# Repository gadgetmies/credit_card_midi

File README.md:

# Credit Card MIDI Controllers

Arduino based, credit card sized, capacitive touch sensing MIDI controllers.

Very much a work in progress. Contributions welcomed 😊!

USB board connector design by @Pinuct: https://github.com/Pinuct/Eagle_PCB_USB_connectors

More info: https://hackaday.io/project/177099-credit-card-midi

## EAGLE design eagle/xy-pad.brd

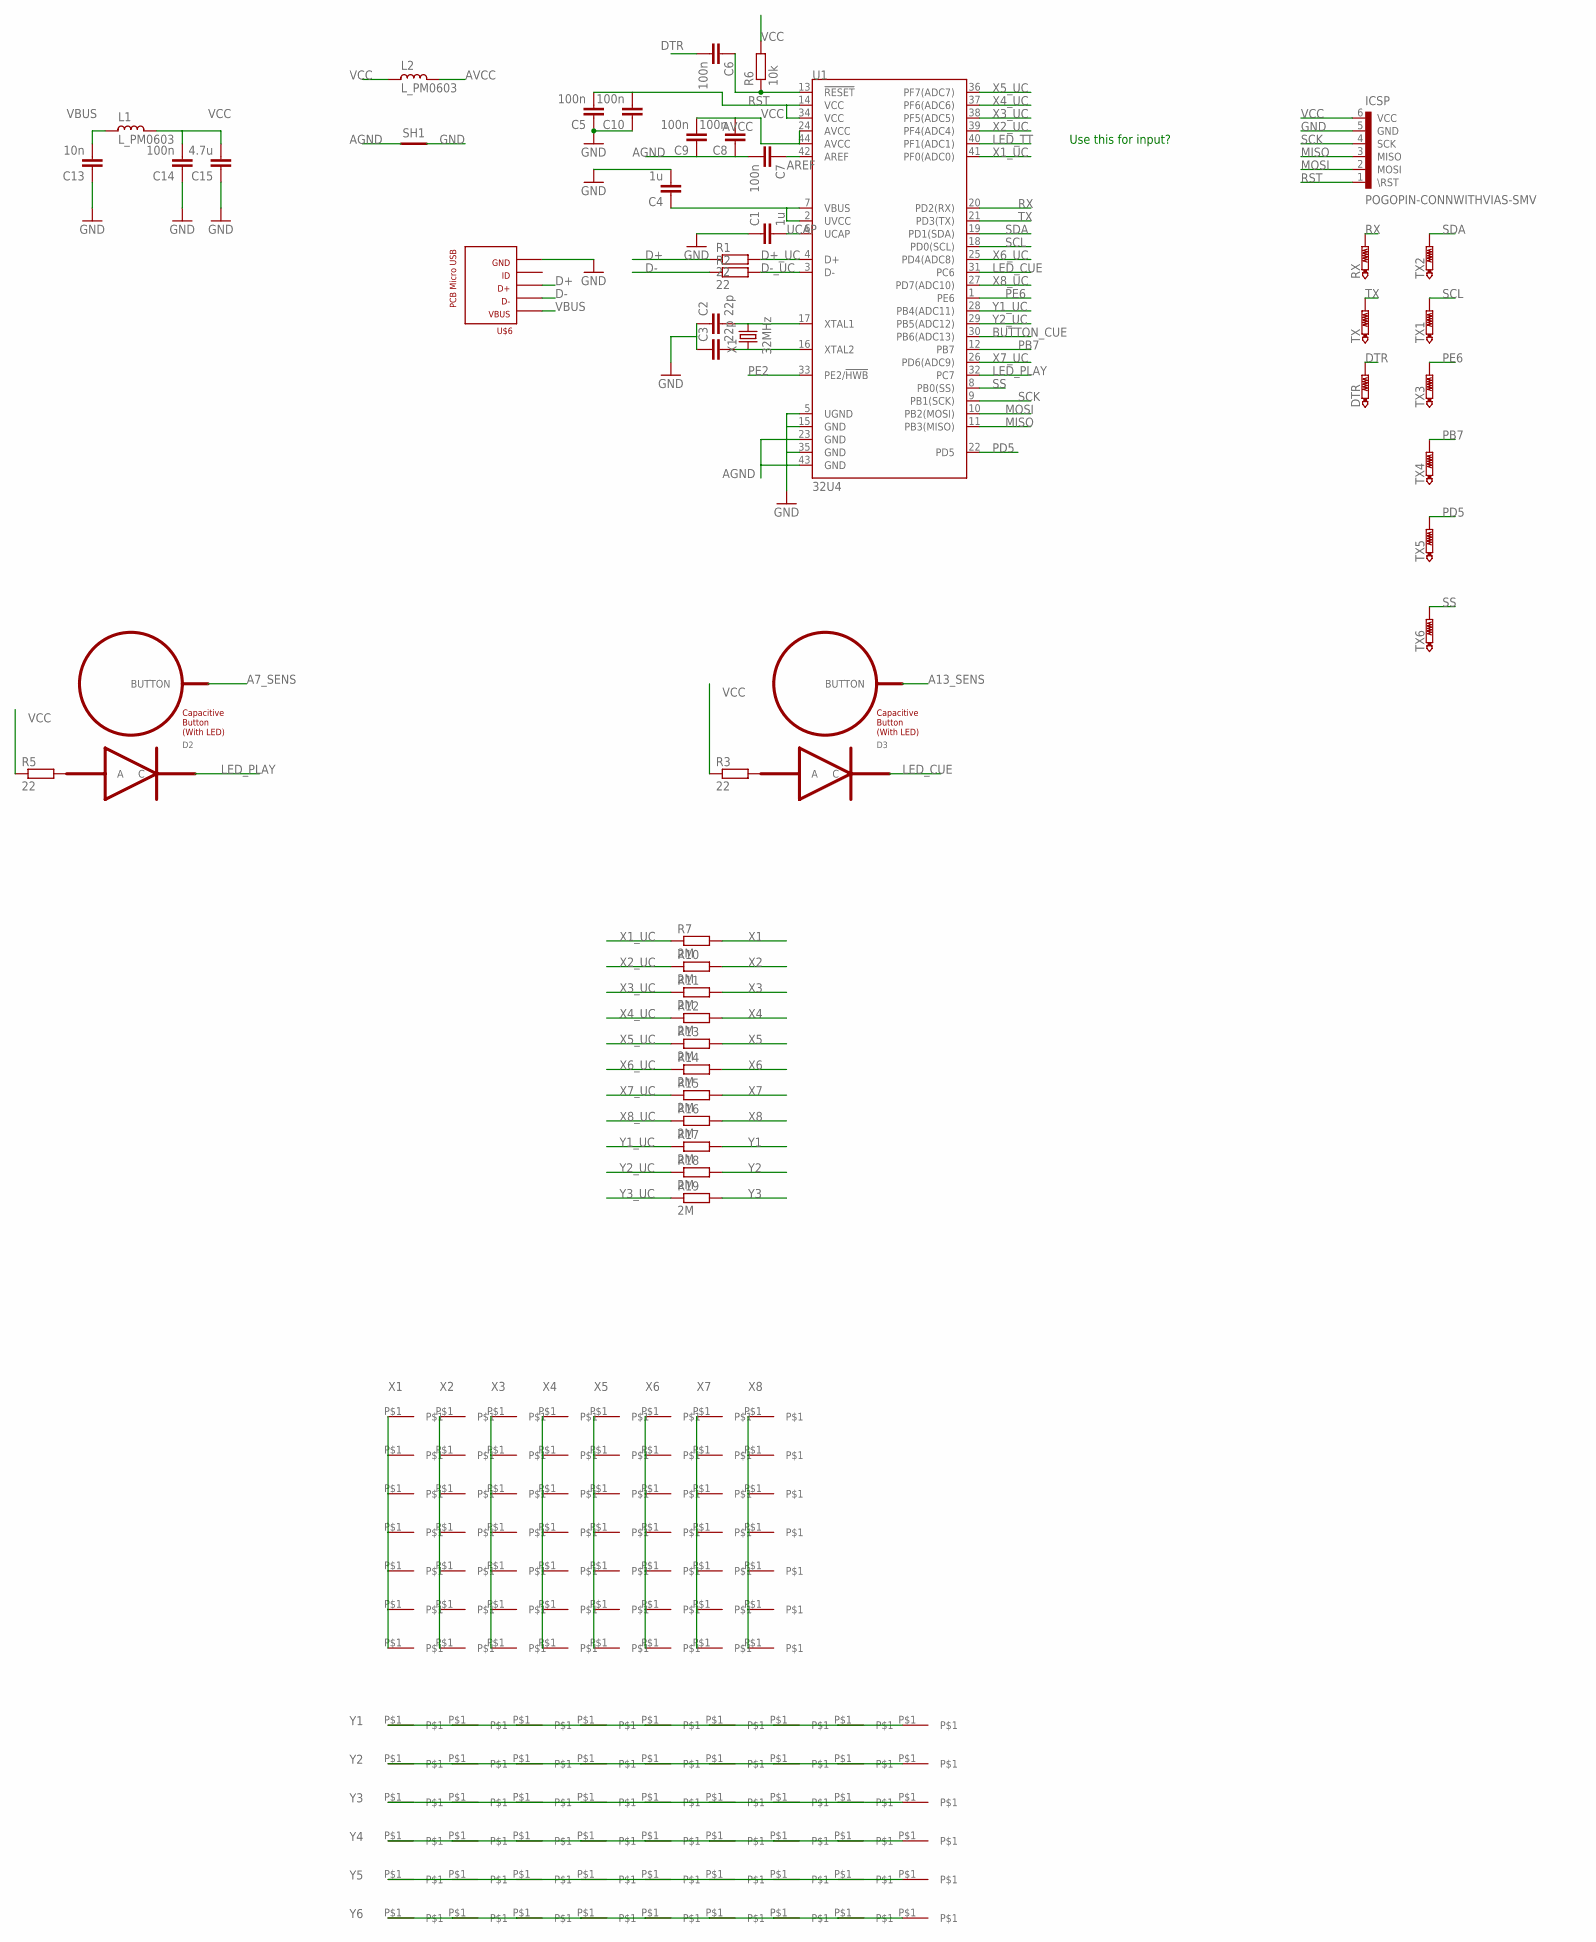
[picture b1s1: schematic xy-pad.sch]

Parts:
C1, C4: 1u; C0402
C2, C3: 22p; C0402
C5, C6, C7, C8, C9, C10, C14: 100n; C0402
C13: 10n; C0402
C15: 4.7u; C0402
D2, D3: LED_BUTTON
DTR: PTR1TP06R; TP06R
ICSP: POGOPIN-CONNWITHVIAS-SMV; POGOPROG-CONN-OH-SMALLERVIAS
L1, L2: L_PM0603; PM0603
R1, R2, R3, R5: 22; R0402
R6: 10k; R0402
R7, R10, R11, R12, R13, R14, R15, R16, R17, R18, R19: 2M; R0402
RX: PTR1TP06R; TP06R
SH1: SHORT; SHORT_TOP-6
TX, TX1, TX2, TX3, TX4, TX5, TX6: PTR1TP06R; TP06R
U1: 32U4; QFN-44
U$1, U$11, U$12, U$13, U$14, U$15, U$16, U$17, U$18, U$19, U$20, U$21, U$22, U$23, U$24, U$25, U$26, U$27, U$28, U$29, U$30, U$31, U$32, U$33, U$34, U$35, U$36, U$37, U$38, U$39, U$40, U$41, U$42, U$43, U$44, U$45, U$46, U$47, U$48, U$49, U$64, U$65, U$66, U$67, U$68, U$69, U$70, U$71, U$72, U$73, U$74, U$75, U$76, U$77, U$78, U$79, U$80, U$81, U$82, U$83, U$84, U$85, U$86, U$87, U$88, U$89, U$90, U$91, U$92, U$93, U$94, U$95, U$96, U$97, U$98, U$99, U$100, U$101, U$102, U$103, U$104, U$105: XY_PAD; DIAMOND_PAD
U$2, U$3, U$4, U$5, U$7, U$8, U$9, U$10, U$50, U$51, U$52, U$53, U$54, U$55, U$56, U$57, U$58, U$59, U$60, U$61, U$62, U$63, U$106, U$107, U$108, U$109, U$110, U$111: XY_PADTRIANGLE; TRIANGLE_PAD
U$6: PCB_MICRO_USB_BSS_2; USB_TYPE_B_SS_2
X1: 32MHz; CRYSTAL-SMD-2.0X1.6MM

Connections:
A7_SENS: D2.BUTTON
A13_SENS: D3.BUTTON
AGND: C7.2, C8.1, C9.1, SH1.1, U1.23 (GND), U1.43 (GND)
AREF: C7.1, U1.42 (AREF)
AVCC: C8.2, C9.2, L2.1, U1.24 (AVCC), U1.44 (AVCC)
BUTTON_CUE: U1.30 (PB6(ADC13))
D+: R1.1, U$6.3
D+_UC: R1.2, U1.4 (D+)
D-: R2.1, U$6.2
D-_UC: R2.2, U1.3 (D-)
DTR: C6.2, DTR.TP
GND: C1.1, C2.1, C3.1, C4.2, C5.1, C10.1, C13.1, C14.1, C15.1, ICSP.5 (GND), SH1.2, U1.5 (UGND), U1.15 (GND), U1.35 (GND), U$6.5
LED_CUE: D3.C, U1.31 (PC6)
LED_PLAY: D2.C, U1.32 (PC7)
LED_TT: U1.40 (PF1(ADC1))
MISO: ICSP.3 (MISO), U1.11 (PB3(MISO))
MOSI: ICSP.2 (MOSI), U1.10 (PB2(MOSI))
unnamed: D3.A, R3.2
unnamed: C2.2, U1.17 (XTAL1), X1.3 (2)
unnamed: C3.2, U1.16 (XTAL2), X1.1
unnamed: D2.A, R5.2
PB7: TX4.TP, U1.12 (PB7)
PD5: TX5.TP, U1.22 (PD5)
PE2: U1.33 (PE2/!HWB)
PE6: TX3.TP, U1.1 (PE6)
RST: C6.1, ICSP.1 (\RST), R6.1, U1.13 (!RESET)
RX: RX.TP, U1.20 (PD2(RX))
SCK: ICSP.4 (SCK), U1.9 (PB1(SCK))
SCL: TX1.TP, U1.18 (PD0(SCL))
SDA: TX2.TP, U1.19 (PD1(SDA))
SS: TX6.TP, U1.8 (PB0(SS))
TX: TX.TP, U1.21 (PD3(TX))
UCAP: C1.2, U1.6 (UCAP)
VBUS: C13.2, L1.2, U$6.1
VCC: C4.1, C5.2, C10.2, C14.2, C15.2, ICSP.6 (VCC), L1.1, L2.2, R3.1, R5.1, R6.2, U1.2 (UVCC), U1.7 (VBUS), U1.14 (VCC), U1.34 (VCC)
X1: R7.2, U$1.P$1, U$2.P$1, U$18.P$1, U$26.P$1, U$34.P$1, U$42.P$1, U$50.P$1
X1_UC: R7.1, U1.41 (PF0(ADC0))
X2: R10.2, U$3.P$1, U$11.P$1, U$19.P$1, U$27.P$1, U$35.P$1, U$43.P$1, U$51.P$1
X2_UC: R10.1, U1.39 (PF4(ADC4))
X3: R11.2, U$4.P$1, U$12.P$1, U$20.P$1, U$28.P$1, U$36.P$1, U$44.P$1, U$52.P$1
X3_UC: R11.1, U1.38 (PF5(ADC5))
X4: R12.2, U$5.P$1, U$13.P$1, U$21.P$1, U$29.P$1, U$37.P$1, U$45.P$1, U$53.P$1
X4_UC: R12.1, U1.37 (PF6(ADC6))
X5: R13.2, U$7.P$1, U$14.P$1, U$22.P$1, U$30.P$1, U$38.P$1, U$46.P$1, U$54.P$1
X5_UC: R13.1, U1.36 (PF7(ADC7))
X6: R14.2, U$8.P$1, U$15.P$1, U$23.P$1, U$31.P$1, U$39.P$1, U$47.P$1, U$55.P$1
X6_UC: R14.1, U1.25 (PD4(ADC8))
X7: R15.2, U$9.P$1, U$16.P$1, U$24.P$1, U$32.P$1, U$40.P$1, U$48.P$1, U$56.P$1
X7_UC: R15.1, U1.26 (PD6(ADC9))
X8: R16.2, U$10.P$1, U$17.P$1, U$25.P$1, U$33.P$1, U$41.P$1, U$49.P$1, U$57.P$1
X8_UC: R16.1, U1.27 (PD7(ADC10))
Y1: R17.2, U$63.P$1, U$69.P$1, U$75.P$1, U$81.P$1, U$87.P$1, U$93.P$1, U$99.P$1, U$105.P$1, U$111.P$1
Y1_UC: R17.1, U1.28 (PB4(ADC11))
Y2: R18.2, U$62.P$1, U$68.P$1, U$74.P$1, U$80.P$1, U$86.P$1, U$92.P$1, U$98.P$1, U$104.P$1, U$110.P$1
Y2_UC: R18.1, U1.29 (PB5(ADC12))
Y3: R19.2, U$61.P$1, U$67.P$1, U$73.P$1, U$79.P$1, U$85.P$1, U$91.P$1, U$97.P$1, U$103.P$1, U$109.P$1
Y3_UC: R19.1
Y4: U$60.P$1, U$66.P$1, U$72.P$1, U$78.P$1, U$84.P$1, U$90.P$1, U$96.P$1, U$102.P$1, U$108.P$1
Y5: U$59.P$1, U$65.P$1, U$71.P$1, U$77.P$1, U$83.P$1, U$89.P$1, U$95.P$1, U$101.P$1, U$107.P$1
Y6: U$58.P$1, U$64.P$1, U$70.P$1, U$76.P$1, U$82.P$1, U$88.P$1, U$94.P$1, U$100.P$1, U$106.P$1

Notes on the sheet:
Use this for input?

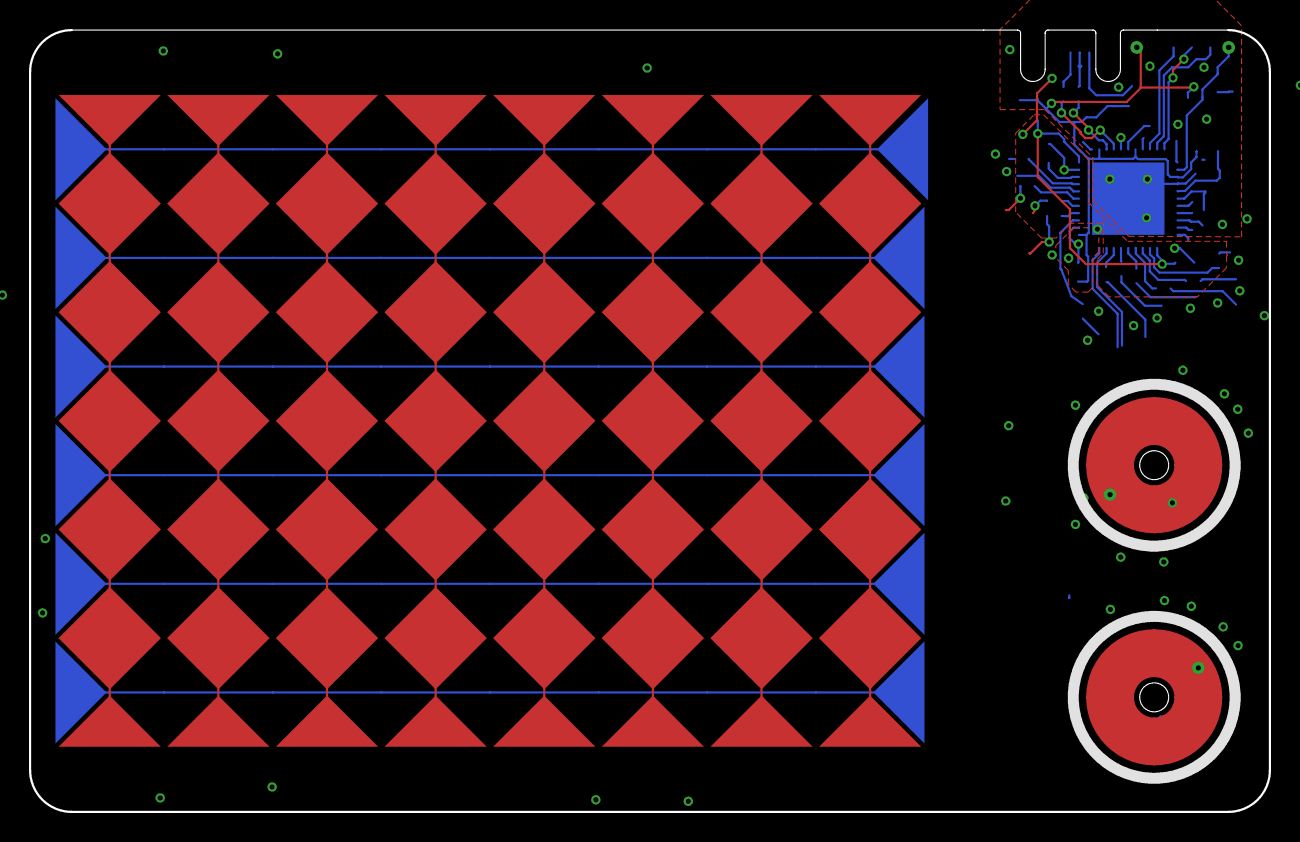
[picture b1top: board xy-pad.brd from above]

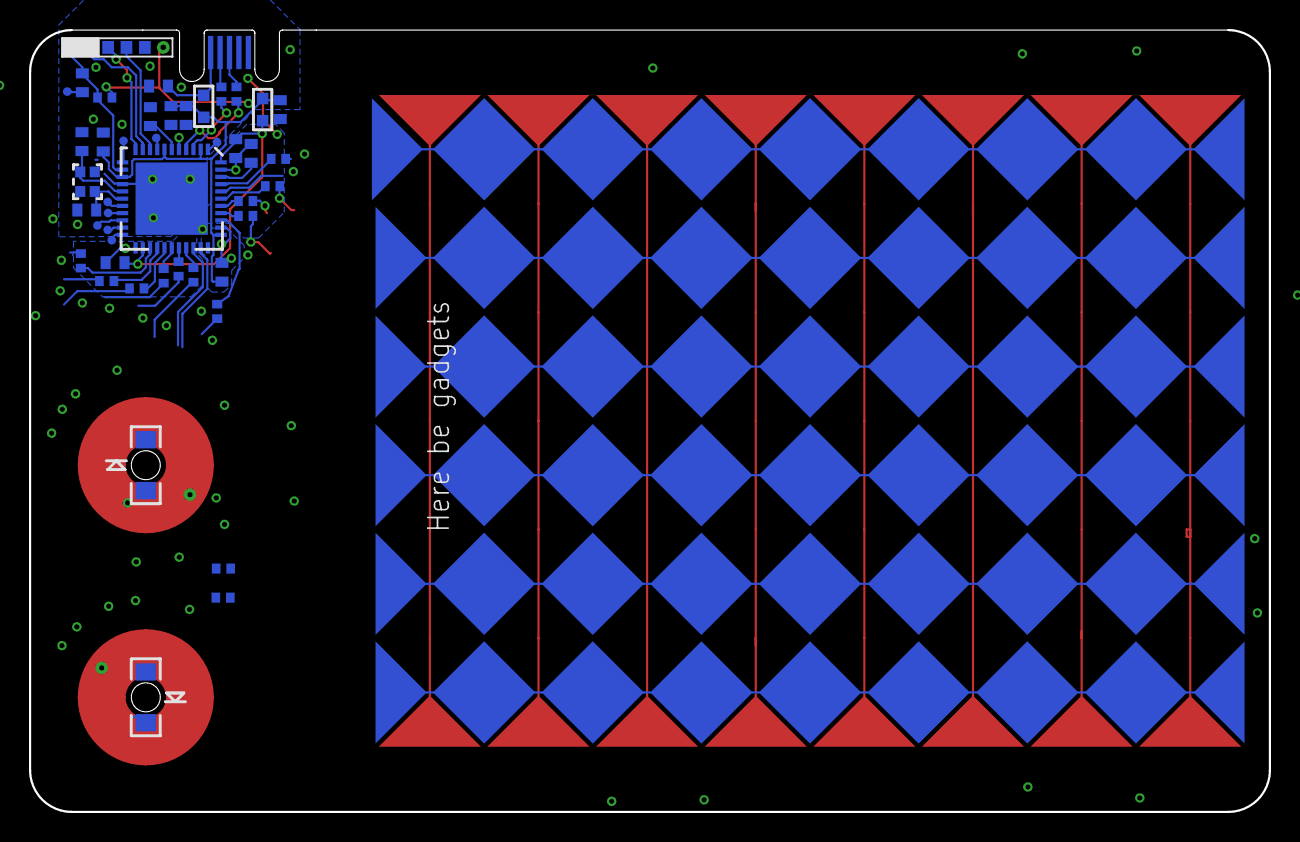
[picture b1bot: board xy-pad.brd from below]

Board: 2 copper layers, 85.6 x 54.0 mm, 157 parts (98 on the bottom side), 54 nets.

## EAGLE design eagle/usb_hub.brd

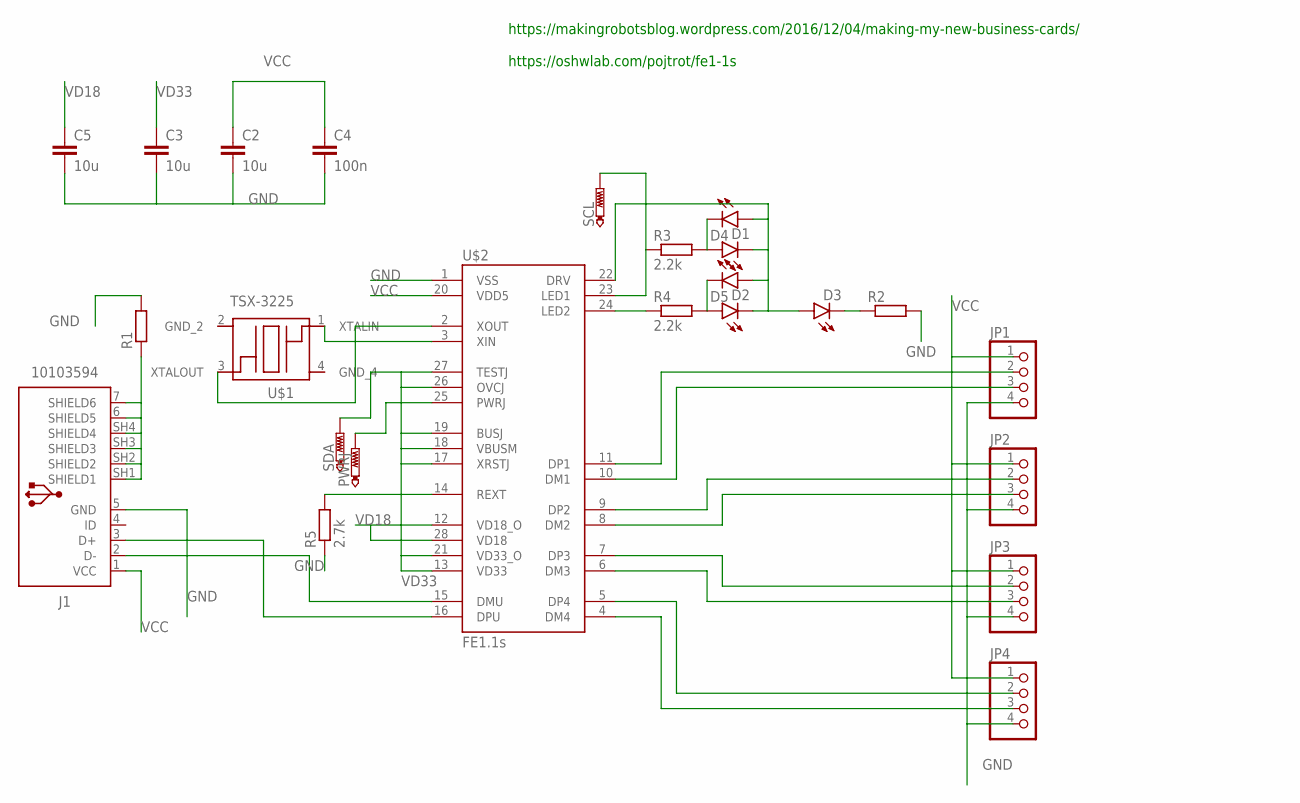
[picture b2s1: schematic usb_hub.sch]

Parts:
C2, C3, C5: 10u; C0805
C4: 100n; C0603
D1, D2, D3, D4, D5: LEDCHIP-LED0603; CHIP-LED0603
J1: 10103594
JP1, JP2, JP3, JP4: PINHD-1X4; 1X04
PWRJ: PTR1B1,27; B1,27
R1, R2: R-EU_R0603; R0603
R3, R4: 2.2k; R0603
R5: 2.7k; R0603
SCL: PTR1B1,27; B1,27
SDA: PTR1B1,27; B1,27
U$1: TSX-3225
U$2: FE1.1S; FE1.1S_SSOP-28

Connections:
GND: C2.2, C3.2, C4.2, C5.2, J1.5 (GND), JP1.4, JP2.4, JP3.4, JP4.4, R1.2, R2.2, R5.1, U$2.1 (VSS)
unnamed: J1.3 (D+), U$2.16 (DPU)
unnamed: J1.2 (D-), U$2.15 (DMU)
unnamed: U$1.1 (XTALIN), U$2.3 (XIN)
unnamed: U$1.3 (XTALOUT), U$2.2 (XOUT)
unnamed: D1.A, D4.C, R3.2
unnamed: D2.A, D5.C, R4.2
unnamed: JP4.3, U$2.4 (DM4)
unnamed: JP4.2, U$2.5 (DP4)
unnamed: JP3.3, U$2.6 (DM3)
unnamed: JP3.2, U$2.7 (DP3)
unnamed: JP2.3, U$2.8 (DM2)
unnamed: JP2.2, U$2.9 (DP2)
unnamed: JP1.3, U$2.10 (DM1)
unnamed: JP1.2, U$2.11 (DP1)
unnamed: R4.1, U$2.24 (LED2)
unnamed: D3.C, R2.1
unnamed: R3.1, SCL.TP, U$2.23 (LED1)
unnamed: D1.C, D2.C, D3.A, D4.A, D5.A, U$2.22 (DRV)
unnamed: PWRJ.TP, U$2.25 (PWRJ)
unnamed: R5.2, U$2.14 (REXT)
SHIELD2: J1.6 (SHIELD5), J1.7 (SHIELD6), J1.SH1 (SHIELD1), J1.SH2 (SHIELD2), J1.SH3 (SHIELD3), J1.SH4 (SHIELD4), R1.1
VCC: C2.1, C4.1, J1.1 (VCC), JP1.1, JP2.1, JP3.1, JP4.1, U$2.20 (VDD5)
VD18: C5.1, U$2.12 (VD18_O), U$2.28 (VD18)
VD33: C3.1, SDA.TP, U$2.13 (VD33), U$2.17 (XRSTJ), U$2.18 (VBUSM), U$2.19 (BUSJ), U$2.21 (VD33_O), U$2.26 (OVCJ), U$2.27 (TESTJ)

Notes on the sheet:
https://makingrobotsblog.wordpress.com/2016/12/04/making-my-new-business-cards/ https://oshwlab.com/pojtrot/fe1-1s

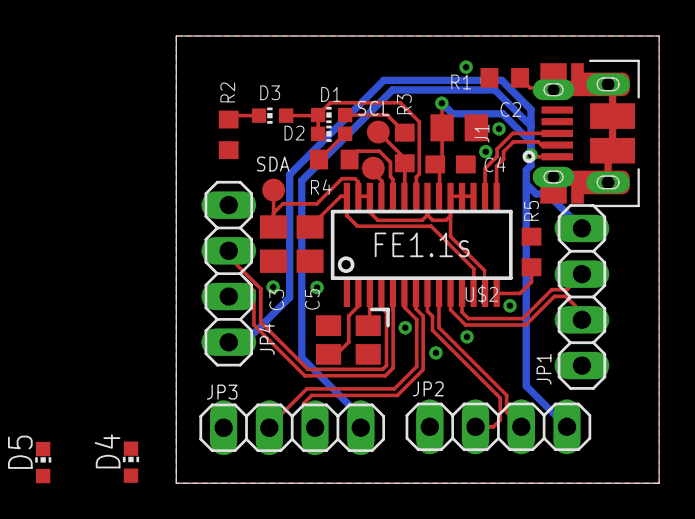
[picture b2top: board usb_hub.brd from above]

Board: 2 copper layers, 26.8 x 24.8 mm, 24 parts (0 on the bottom side), 25 nets.

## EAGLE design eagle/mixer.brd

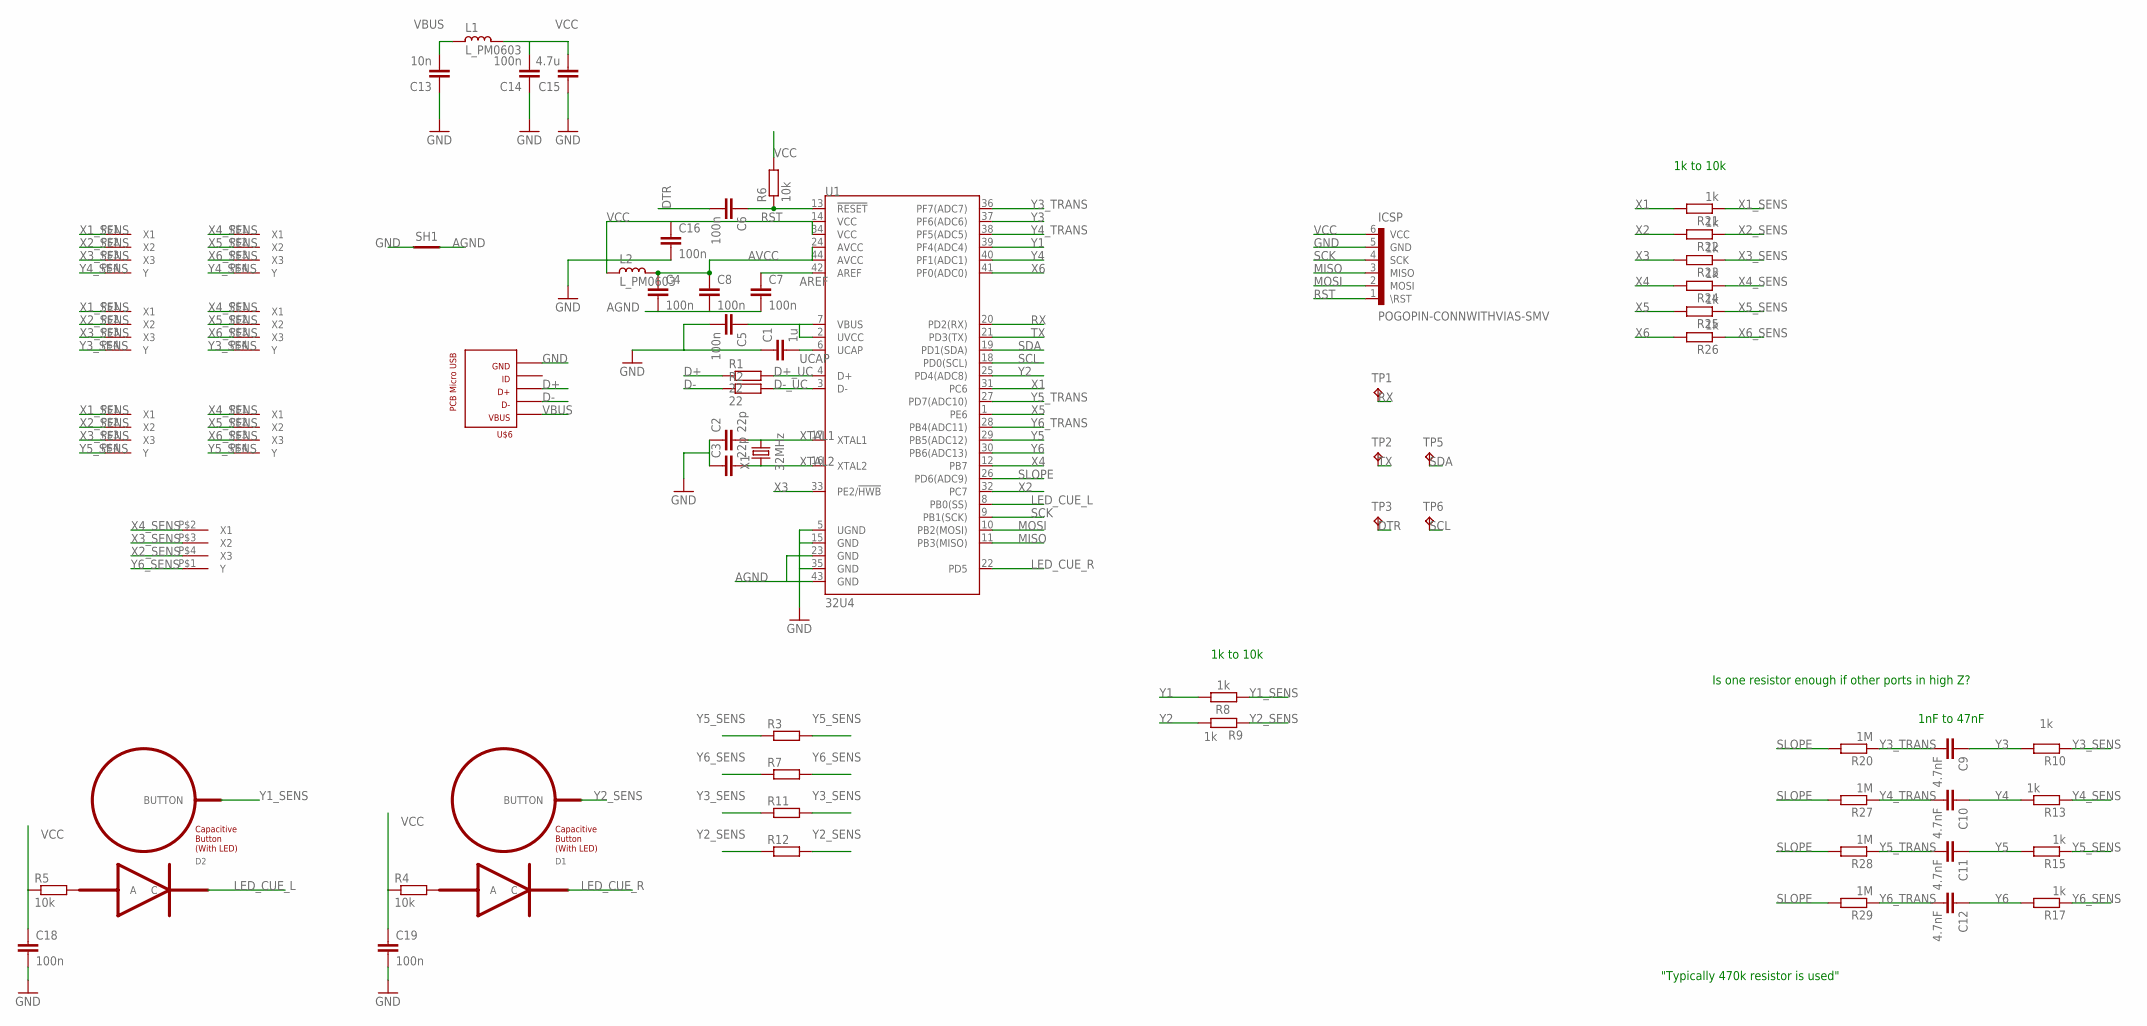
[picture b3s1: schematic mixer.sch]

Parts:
C1: 1u; C0402
C2, C3: 22p; C0402
C4, C5, C6, C7, C8, C14, C16, C18, C19: 100n; C0402
C9, C10, C11, C12: 4.7nF; C0402
C13: 10n; C0402
C15: 4.7u; C0402
D1, D2: LED_BUTTON
ICSP: POGOPIN-CONNWITHVIAS-SMV; POGOPROG-CONN-OH-SMALLERVIAS
L1, L2: L_PM0603; PM0603
R1, R2: 22; R0402
R3, R7, R11, R12: R-EU_R0603; R0603
R4, R5, R6: 10k; R0402
R8, R9, R10, R13, R15, R17, R21, R22, R23, R24, R25, R26: 1k; R0402
R20, R27, R28, R29: 1M; R0402
SH1: SHORT; SHORT_TOP-6
TP1, TP2, TP3, TP5, TP6: TPTP06R; TP06R
U1: 32U4; QFN-44
U$1, U$2, U$3, U$4, U$5, U$7: EQ_MUTUAL; SMALL_EQ
U$6: PCB_MICRO_USB_BSS_2; USB_TYPE_B_SS_2
U$8: SLIDER
X1: 32MHz; CRYSTAL-SMD-2.0X1.6MM

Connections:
AGND: C4.2, C7.2, C8.2, SH1.2, U1.23 (GND), U1.43 (GND)
AREF: C7.1, U1.42 (AREF)
AVCC: C4.1, C8.1, L2.1, U1.24 (AVCC), U1.44 (AVCC)
D+: R1.1, U$6.3
D+_UC: R1.2, U1.4 (D+)
D-: R2.1, U$6.2
D-_UC: R2.2, U1.3 (D-)
DTR: C6.2, TP3.TP
GND: C1.1, C2.1, C3.1, C5.2, C13.1, C14.1, C15.1, C16.2, C18.2, C19.2, ICSP.5 (GND), SH1.1, U1.5 (UGND), U1.15 (GND), U1.35 (GND), U$6.5
LED_CUE_L: D2.C, U1.8 (PB0(SS))
LED_CUE_R: D1.C, U1.22 (PD5)
MISO: ICSP.3 (MISO), U1.11 (PB3(MISO))
MOSI: ICSP.2 (MOSI), U1.10 (PB2(MOSI))
unnamed: D1.A, R4.2
unnamed: D2.A, R5.2
RST: C6.1, ICSP.1 (\RST), R6.1, U1.13 (!RESET)
RX: TP1.TP, U1.20 (PD2(RX))
SCK: ICSP.4 (SCK), U1.9 (PB1(SCK))
SCL: TP6.TP, U1.18 (PD0(SCL))
SDA: TP5.TP, U1.19 (PD1(SDA))
SLOPE: R20.2, R27.2, R28.2, R29.2, U1.26 (PD6(ADC9))
TX: TP2.TP, U1.21 (PD3(TX))
UCAP: C1.2, U1.6 (UCAP)
VBUS: C13.2, L1.2, U$6.1
VCC: C5.1, C14.2, C15.2, C16.1, C18.1, C19.1, ICSP.6 (VCC), L1.1, L2.2, R4.1, R5.1, R6.2, U1.2 (UVCC), U1.7 (VBUS), U1.14 (VCC), U1.34 (VCC)
X1: R21.2, U1.31 (PC6)
X1_SENS: R21.1, U$1.P$1 (X1), U$2.P$1 (X1), U$3.P$1 (X1)
X2: R22.2, U1.32 (PC7)
X2_SENS: R22.1, U$1.P$2 (X2), U$2.P$2 (X2), U$3.P$2 (X2), U$8.P$4 (X3)
X3: R23.2, U1.33 (PE2/!HWB)
X3_SENS: R23.1, U$1.P$3 (X3), U$2.P$3 (X3), U$3.P$3 (X3), U$8.P$3 (X2)
X4: R24.2, U1.12 (PB7)
X4_SENS: R24.1, U$4.P$1 (X1), U$5.P$1 (X1), U$7.P$1 (X1), U$8.P$2 (X1)
X5: R25.2, U1.1 (PE6)
X5_SENS: R25.1, U$4.P$2 (X2), U$5.P$2 (X2), U$7.P$2 (X2)
X6: R26.2, U1.41 (PF0(ADC0))
X6_SENS: R26.1, U$4.P$3 (X3), U$5.P$3 (X3), U$7.P$3 (X3)
XTAL1: C2.2, U1.17 (XTAL1), X1.3 (2)
XTAL2: C3.2, U1.16 (XTAL2), X1.1
Y1: R8.2, U1.39 (PF4(ADC4))
Y1_SENS: D2.BUTTON, R8.1
Y2: R9.2, U1.25 (PD4(ADC8))
Y2_SENS: D1.BUTTON, R9.1, R12.1, R12.2
Y3: C9.1, R10.2, U1.37 (PF6(ADC6))
Y3_SENS: R10.1, R11.1, R11.2, U$2.P$4 (Y), U$5.P$4 (Y)
Y3_TRANS: C9.2, R20.1, U1.36 (PF7(ADC7))
Y4: C10.1, R13.2, U1.40 (PF1(ADC1))
Y4_SENS: R13.1, U$1.P$4 (Y), U$4.P$4 (Y)
Y4_TRANS: C10.2, R27.1, U1.38 (PF5(ADC5))
Y5: C11.1, R15.2, U1.29 (PB5(ADC12))
Y5_SENS: R3.1, R3.2, R15.1, U$3.P$4 (Y), U$7.P$4 (Y)
Y5_TRANS: C11.2, R28.1, U1.27 (PD7(ADC10))
Y6: C12.1, R17.2, U1.30 (PB6(ADC13))
Y6_SENS: R7.1, R7.2, R17.1, U$8.P$1 (Y)
Y6_TRANS: C12.2, R29.1, U1.28 (PB4(ADC11))

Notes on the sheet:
Is one resistor enough if other ports in high Z?
"Typically 470k resistor is used"
1nF to 47nF
1k to 10k

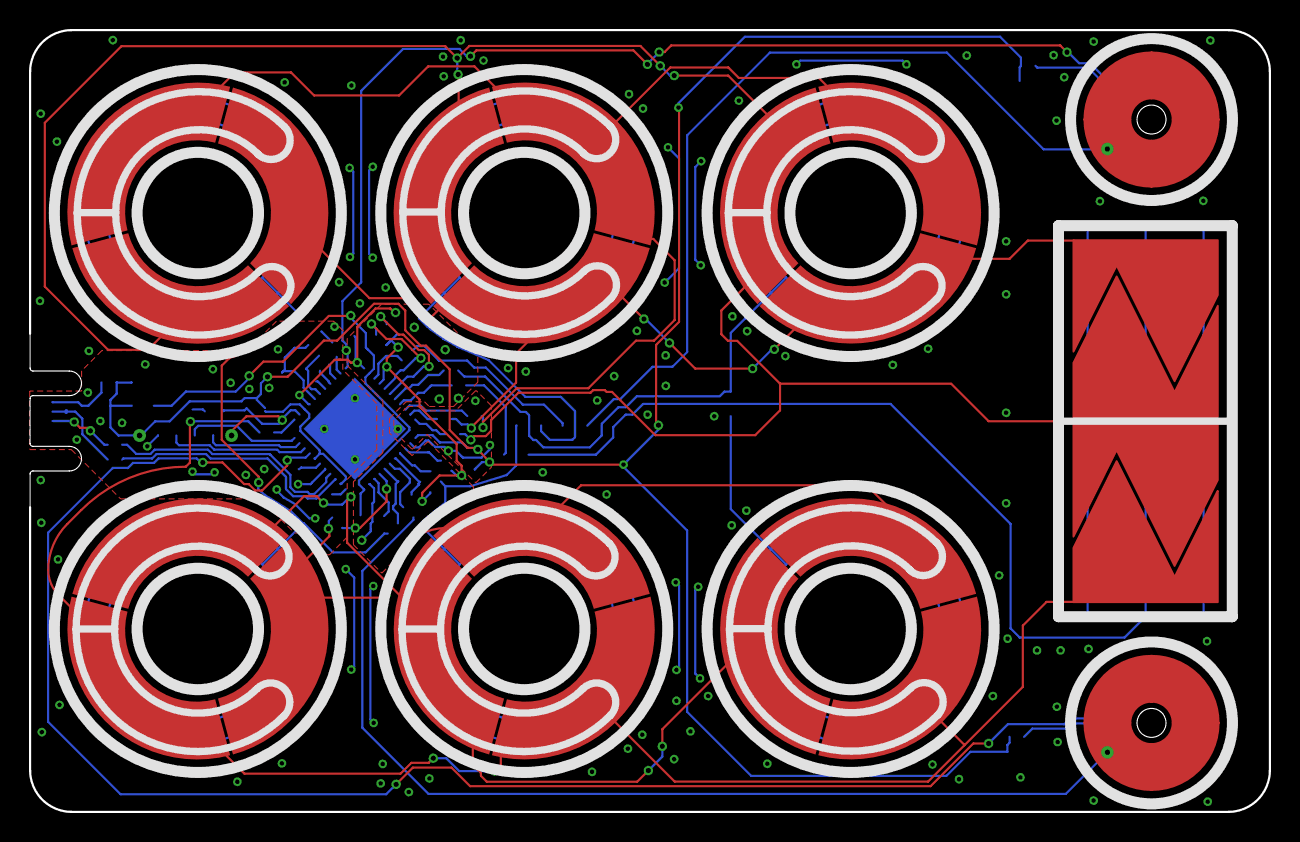
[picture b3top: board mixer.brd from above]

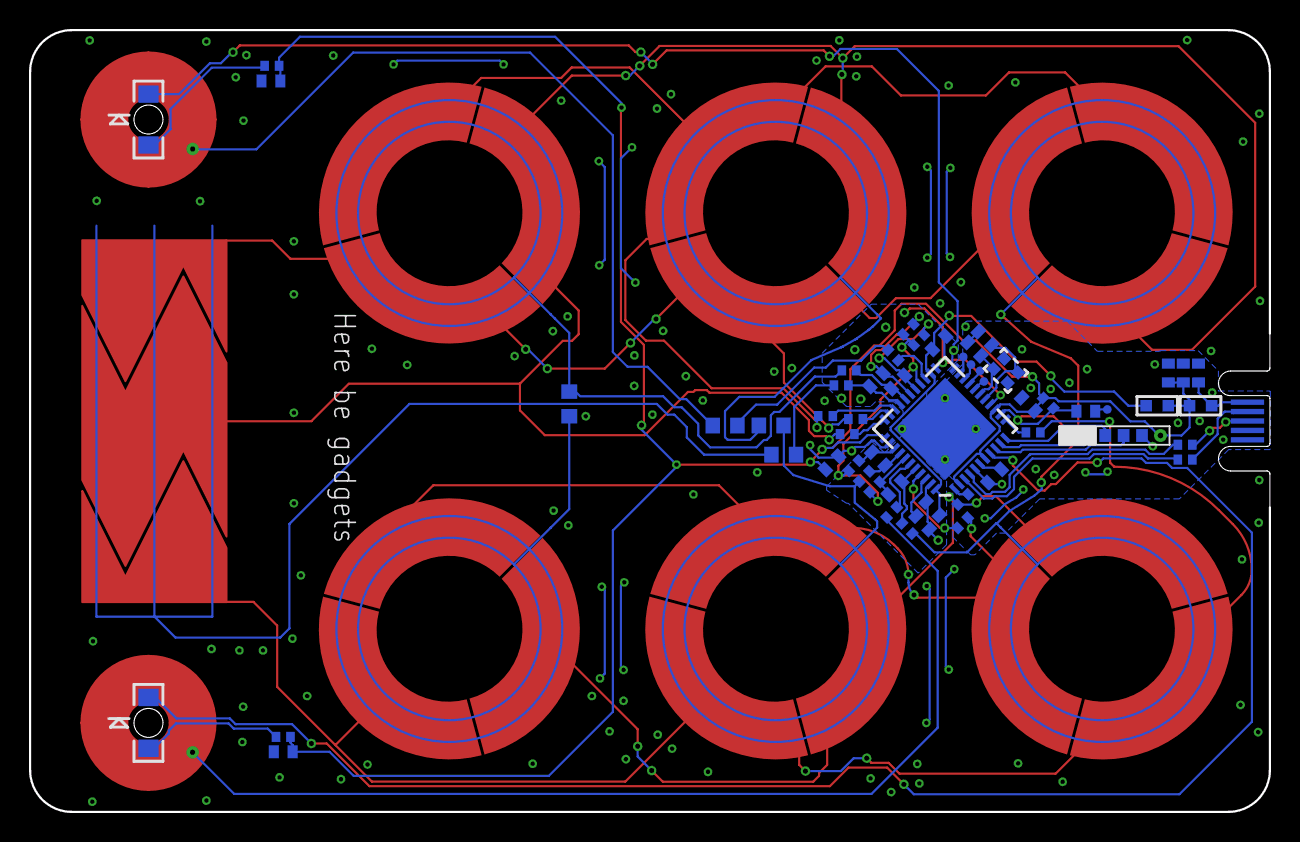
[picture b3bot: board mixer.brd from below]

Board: 2 copper layers, 85.6 x 54.0 mm, 64 parts (54 on the bottom side), 55 nets.

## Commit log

2021-02-21 Create LICENSE
2022-11-14 Add USB hub and XY-pad boards

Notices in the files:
parts and their libraries:
SparkFun-IC-Microcontroller: Licensing: Creative Commons ShareAlike 4.0 International - https://creativecommons.org/licenses/by-sa/4.0
rc-master-smd: Copyright (C) 2007, Bob Starr
